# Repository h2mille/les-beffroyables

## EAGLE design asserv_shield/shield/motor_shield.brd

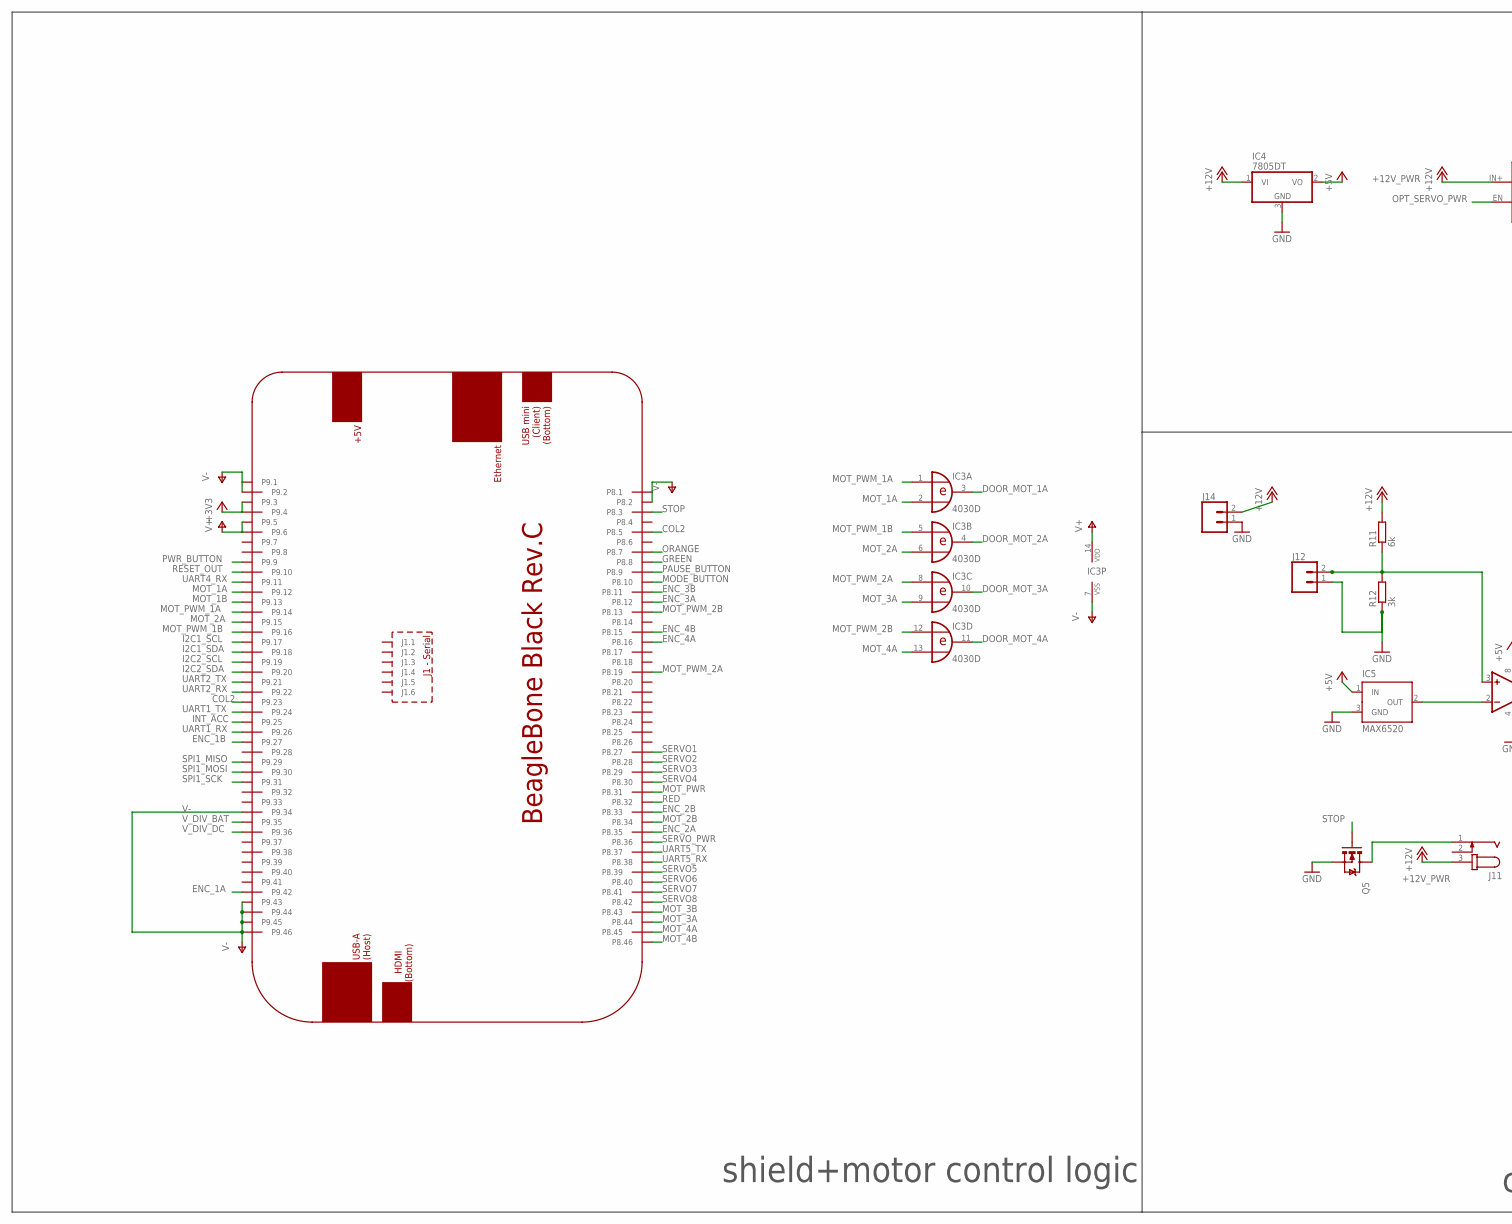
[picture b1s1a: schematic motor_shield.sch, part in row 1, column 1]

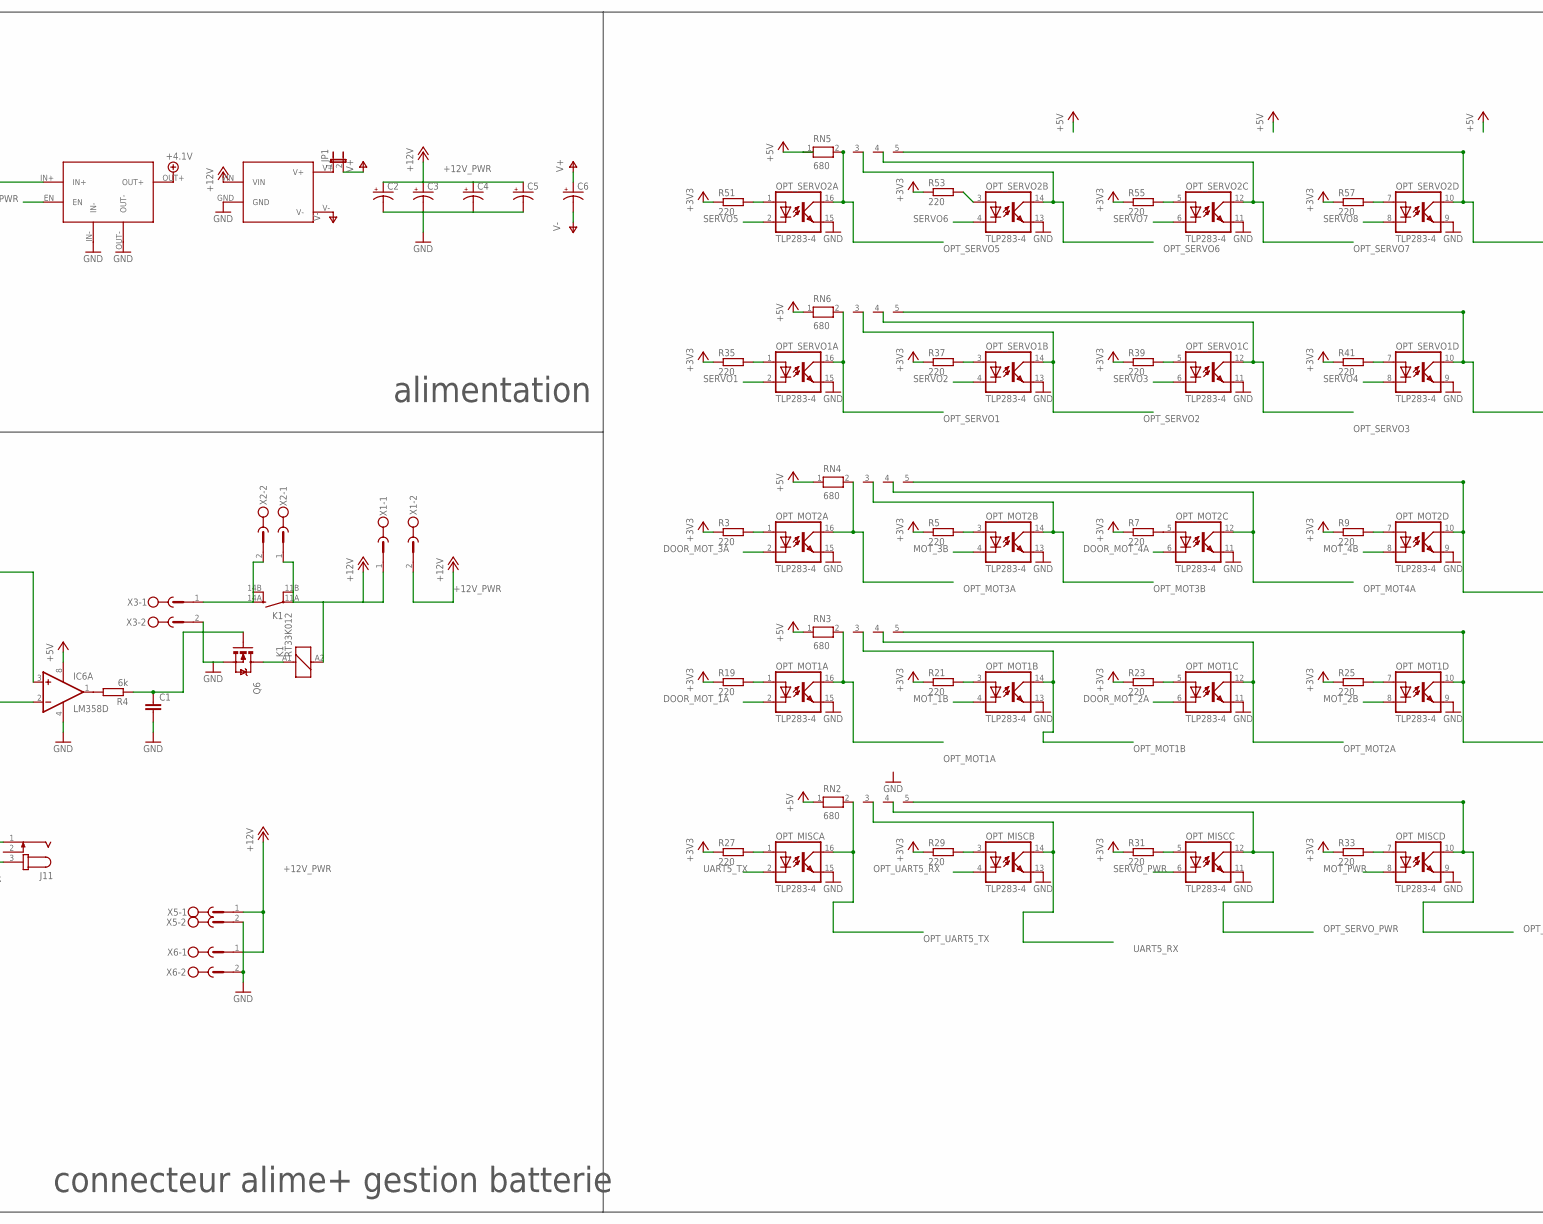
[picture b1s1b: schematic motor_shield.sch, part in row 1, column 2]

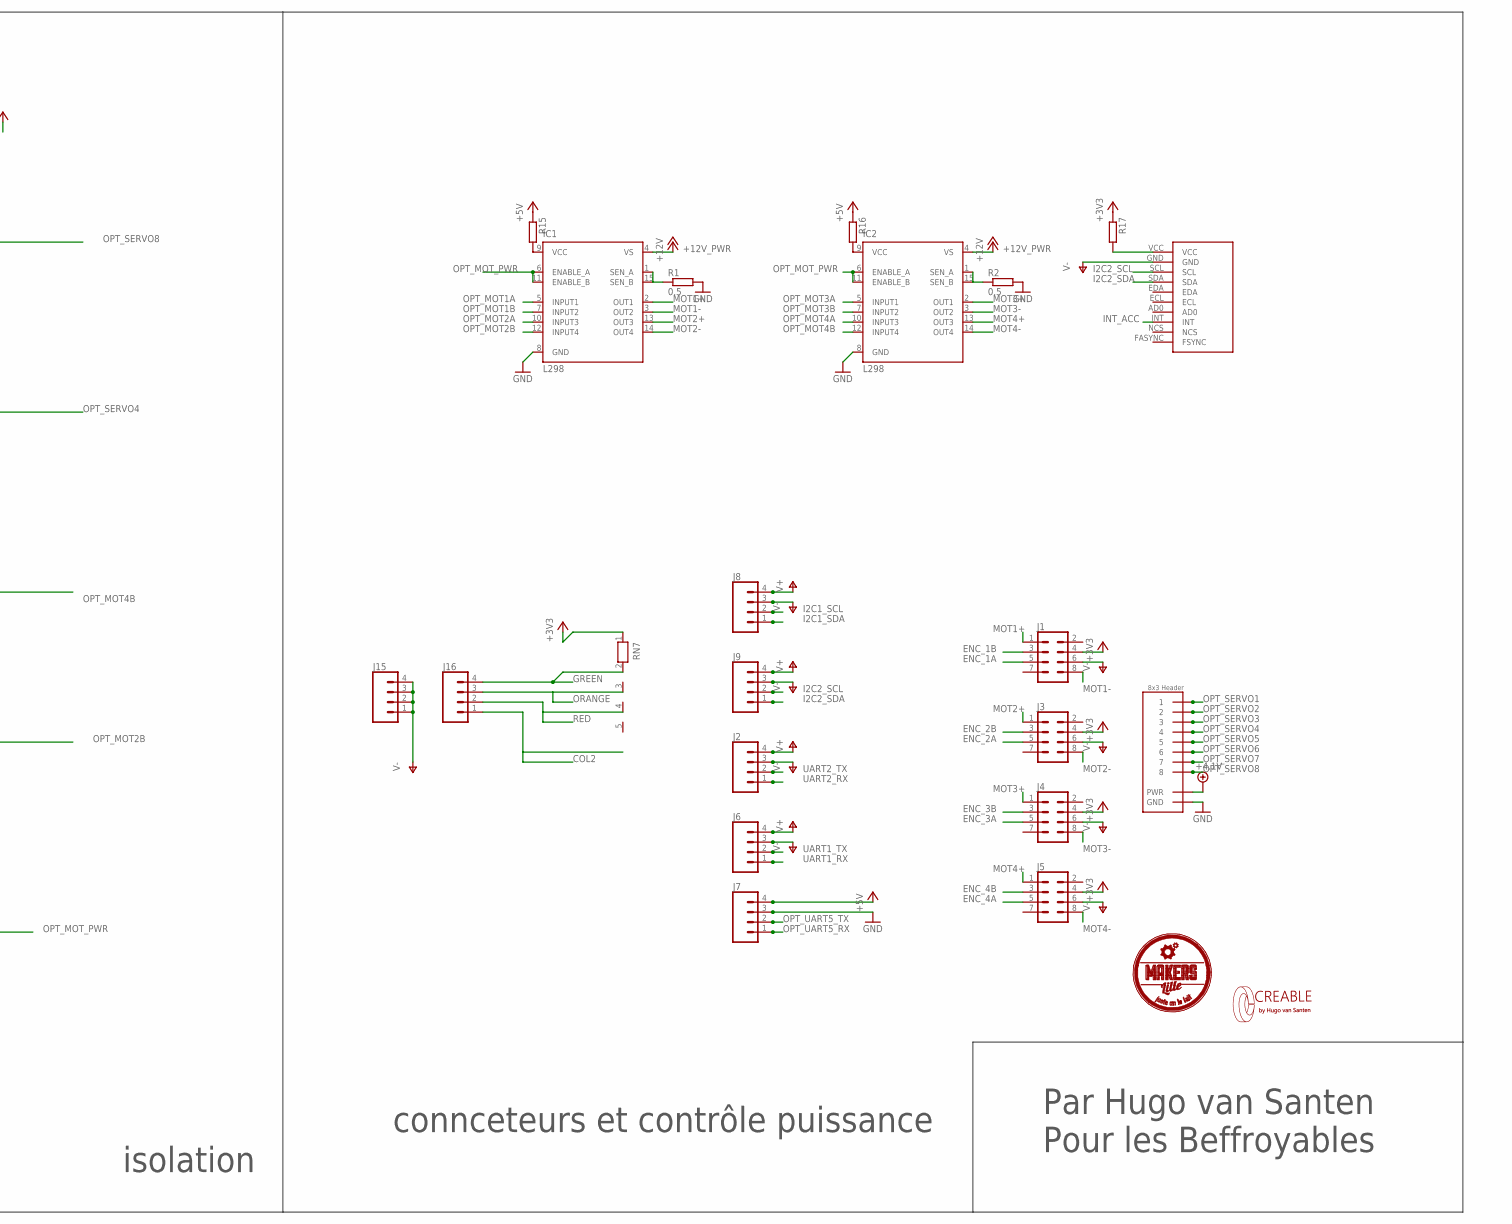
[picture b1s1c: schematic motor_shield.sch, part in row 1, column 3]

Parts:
C1: SPARKFUN-CAPACITORS_CAP0805; SPARKFUN-CAPACITORS_0805
C2, C3, C4, C5, C6: CPOL-US140CLH-1010; ADAFRUIT_140CLH-1010
IC1, IC2: L298; MULTIWATT-15
IC3: 4030D; SO14
IC4: 7805DT; TO252
IC5: MAX6520; SOT23
IC6: LM358D; SO08
J1, J3, J4, J5: CONN_04X2; 2X4
J2, J6, J7, J8, J9: CONN_04POLAR; MOLEX-1X4
J11: JACK-PLUG1; SPC4078
J12, J14: CONN_02POLAR_LOCK; MOLEX-1X2_LOCK
J15, J16: CONN_04; 1X04
JP1: JP1E; JP1
K1: RT33K012; RT-N/O16A5
OPT_MISC: TLP283-4; MINI-FLAT-16
OPT_MOT1, OPT_MOT2: TLP283-4; MINI-FLAT-16
OPT_SERVO1, OPT_SERVO2: TLP283-4; MINI-FLAT-16
PCB1: BEAGLEBONE_BLACK_CAPE
Q5, Q6: STRAWSON_EAGLE_LIB_MOSFET-NCHANNEL; STRAWSON_EAGLE_LIB_SO08-TIGHT
R1, R2: 0.5; M0805
R3, R5, R7, R9, R19, R21, R23, R25, R27, R29, R31, R33, R35, R37, R39, R41, R51, R53, R55, R57: 220; M0805
R4, R11: 6k; M0805
R12: 3k; M0805
R15, R16, R17: R-EU_R0402; R0402
RN2, RN3, RN4, RN5, RN6: 680; RN-5
RN7: RN04; RN-5
U$1: WRA-YMD
U$2: MPU9220; MPU9250
U$3: LOGO
U$4: STRAWSON_EAGLE_LIB_SERVO_HEADERS_8X; STRAWSON_EAGLE_LIB_3X8_0.1"_HEADER
U$5: XL6009
U$6: LOGO_MAKERS
X1, X2, X3, X5, X6: MSTBV2

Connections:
+3V3: J1.4, J3.4, J4.4, J5.4, PCB1.P9.3, PCB1.P9.4, R3.1, R5.1, R7.1, R9.1, R17.1, R19.1, R21.1, R23.1, R25.1, R27.1, R29.1, R31.1, R33.1, R35.1, R37.1, R39.1, R41.1, R51.1, R53.1, R55.1, R57.1, RN7.1
+4.1V: U$4.P$7 (PWR), U$4.P$8 (PWR), U$4.P$9 (PWR), U$4.P$10 (PWR), U$4.P$11 (PWR), U$4.P$12 (PWR), U$4.P$21 (PWR), U$4.P$22 (PWR), U$5.OUT+
+5V: IC4.2 (VO), IC5.1 (IN), IC6.8 (V+), J7.4, R15.1, R16.1, RN2.1, RN3.1, RN4.1, RN5.1, RN6.1
+12V: IC4.1 (VI), J14.2, K1.11A (PA), K1.11B (PB), K1.A2 (2), R11.2, U$1.VIN, X1.1, X2.1
+12V_PWR: C2.+, C3.+, C4.+, C5.+, IC1.4 (VS), IC2.4 (VS), J11.3, U$5.IN+, X1.2, X5.1, X6.1
COL2: J16.1, PCB1.P8.5, PCB1.P9.23
DOOR_MOT_1A: IC3.3 (O), OPT_MOT1.2 (C)
DOOR_MOT_2A: IC3.4 (O), OPT_MOT1.6 (C)
DOOR_MOT_3A: IC3.10 (O), OPT_MOT2.2 (C)
DOOR_MOT_4A: IC3.11 (O), OPT_MOT2.6 (C)
ENC_1A: J1.5, PCB1.P9.42
ENC_1B: J1.3, PCB1.P9.27
ENC_2A: J3.5, PCB1.P8.35
ENC_2B: J3.3, PCB1.P8.33
ENC_3A: J4.5, PCB1.P8.12
ENC_3B: J4.3, PCB1.P8.11
ENC_4A: J5.5, PCB1.P8.16
ENC_4B: J5.3, PCB1.P8.15
GND: C1.2, C2.-, C3.-, C4.-, C5.-, IC1.8 (GND), IC2.8 (GND), IC4.3 (GND), IC5.3 (GND), IC6.4 (V-), J7.3, J12.1, J14.1, OPT_MISC.9 (EMIT), OPT_MISC.11 (EMIT), OPT_MISC.13 (EMIT), OPT_MISC.15 (EMIT), OPT_MOT1.9 (EMIT), OPT_MOT1.11 (EMIT), OPT_MOT1.13 (EMIT), OPT_MOT1.15 (EMIT), OPT_MOT2.9 (EMIT), OPT_MOT2.11 (EMIT), OPT_MOT2.13 (EMIT), OPT_MOT2.15 (EMIT), OPT_SERVO1.9 (EMIT), OPT_SERVO1.11 (EMIT), OPT_SERVO1.13 (EMIT), OPT_SERVO1.15 (EMIT), OPT_SERVO2.9 (EMIT), OPT_SERVO2.11 (EMIT), OPT_SERVO2.13 (EMIT), OPT_SERVO2.15 (EMIT), Q5.1 (S), Q5.2 (S), Q5.3 (S), Q6.1 (S), Q6.2 (S), Q6.3 (S), R1.2, R2.2, R12.1, U$1.GND, U$4.P$13 (GND), U$4.P$14 (GND), U$4.P$15 (GND), U$4.P$16 (GND), U$4.P$17 (GND), U$4.P$18 (GND), U$4.P$23 (GND), U$4.P$24 (GND), U$5.IN-, U$5.OUT-, X3.2, X5.2, X6.2
GREEN: J16.4, PCB1.P8.8, RN7.2
I2C1_SCL: J8.2, PCB1.P9.17
I2C1_SDA: J8.1, PCB1.P9.18
I2C2_SCL: J9.2, PCB1.P9.19, U$2.SCL
I2C2_SDA: J9.1, PCB1.P9.20, U$2.SDA
INT_ACC: PCB1.P9.25, U$2.INT
MODE_BUTTON: PCB1.P8.10
MOT1+: IC1.2 (OUT1), J1.1
MOT1-: IC1.3 (OUT2), J1.8
MOT2+: IC1.13 (OUT3), J3.1
MOT2-: IC1.14 (OUT4), J3.8
MOT3+: IC2.2 (OUT1), J4.1
MOT3-: IC2.3 (OUT2), J4.8
MOT4+: IC2.13 (OUT3), J5.1
MOT4-: IC2.14 (OUT4), J5.8
MOT_1A: IC3.2 (I1), PCB1.P9.12
MOT_1B: OPT_MOT1.4 (C), PCB1.P9.13
MOT_2A: IC3.6 (I1), PCB1.P9.15
MOT_2B: OPT_MOT1.8 (C), PCB1.P8.34
MOT_3A: IC3.9 (I1), PCB1.P8.44
MOT_3B: OPT_MOT2.4 (C), PCB1.P8.43
MOT_4A: IC3.13 (I1), PCB1.P8.45
MOT_4B: OPT_MOT2.8 (C), PCB1.P8.46
MOT_PWM_1A: IC3.1 (I0), PCB1.P9.14
MOT_PWM_1B: IC3.5 (I0), PCB1.P9.16
MOT_PWM_2A: IC3.8 (I0), PCB1.P8.19
MOT_PWM_2B: IC3.12 (I0), PCB1.P8.13
MOT_PWR: OPT_MISC.8 (C), PCB1.P8.31
unnamed: OPT_SERVO2.1 (A), R51.2
unnamed: OPT_SERVO2.3 (A), R53.2
unnamed: OPT_MISC.1 (A), R27.2
unnamed: IC1.1 (SEN_A), IC1.15 (SEN_B), R1.1
unnamed: IC2.1 (SEN_A), IC2.15 (SEN_B), R2.1
unnamed: OPT_SERVO2.7 (A), R57.2
unnamed: OPT_SERVO1.1 (A), R35.2
unnamed: OPT_MOT2.5 (A), R7.2
unnamed: J11.1, Q5.5 (D), Q5.6 (D), Q5.7 (D), Q5.8 (D)
unnamed: OPT_SERVO1.3 (A), R37.2
unnamed: OPT_SERVO1.7 (A), R41.2
unnamed: OPT_MOT2.1 (A), R3.2
unnamed: OPT_MOT2.3 (A), R5.2
unnamed: OPT_MOT2.7 (A), R9.2
unnamed: OPT_MOT1.3 (A), R21.2
unnamed: OPT_MOT1.1 (A), R19.2
unnamed: OPT_MOT1.7 (A), R25.2
unnamed: OPT_MOT1.5 (A), R23.2
unnamed: OPT_SERVO1.5 (A), R39.2
unnamed: OPT_MISC.3 (A), R29.2
unnamed: OPT_MISC.7 (A), R33.2
unnamed: OPT_SERVO2.5 (A), R55.2
unnamed: IC5.2 (OUT), IC6.2 (-IN)
unnamed: OPT_MISC.5 (A), R31.2
unnamed: IC6.1 (OUT), R4.2
unnamed: K1.14A (SA), K1.14B (SB), X2.2, X3.1
unnamed: K1.A1 (1), Q6.5 (D), Q6.6 (D), Q6.7 (D), Q6.8 (D)
unnamed: IC6.3 (+IN), J12.2, R11.1, R12.2
unnamed: C1.1, Q6.4 (G), R4.1
unnamed: JP1.1, U$1.V+
unnamed: IC1.9 (VCC), R15.2
unnamed: IC2.9 (VCC), R16.2
unnamed: R17.2, U$2.VCC
OPT_MOT1A: IC1.5 (INPUT1), OPT_MOT1.16 (COL), RN3.2
OPT_MOT1B: IC1.7 (INPUT2), OPT_MOT1.14 (COL), RN3.3
OPT_MOT2A: IC1.10 (INPUT3), OPT_MOT1.12 (COL), RN3.4
OPT_MOT2B: IC1.12 (INPUT4), OPT_MOT1.10 (COL), RN3.5
OPT_MOT3A: IC2.5 (INPUT1), OPT_MOT2.16 (COL), RN4.2
OPT_MOT3B: IC2.7 (INPUT2), OPT_MOT2.14 (COL), RN4.3
OPT_MOT4A: IC2.10 (INPUT3), OPT_MOT2.12 (COL), RN4.4
OPT_MOT4B: IC2.12 (INPUT4), OPT_MOT2.10 (COL), RN4.5
OPT_MOT_PWR: IC1.6 (ENABLE_A), IC1.11 (ENABLE_B), IC2.6 (ENABLE_A), IC2.11 (ENABLE_B), OPT_MISC.10 (COL), RN2.5
OPT_SERVO1: OPT_SERVO1.16 (COL), RN6.2, U$4.P$1 (1)
OPT_SERVO2: OPT_SERVO1.14 (COL), RN6.3, U$4.P$2 (2)
OPT_SERVO3: OPT_SERVO1.12 (COL), RN6.4, U$4.P$3 (3)
OPT_SERVO4: OPT_SERVO1.10 (COL), RN6.5, U$4.P$4 (4)
OPT_SERVO5: OPT_SERVO2.16 (COL), RN5.2, U$4.P$5 (5)
OPT_SERVO6: OPT_SERVO2.14 (COL), RN5.3, U$4.P$6 (6)
OPT_SERVO7: OPT_SERVO2.12 (COL), RN5.4, U$4.P$19 (7)
OPT_SERVO8: OPT_SERVO2.10 (COL), RN5.5, U$4.P$20 (8)
OPT_SERVO_PWR: OPT_MISC.12 (COL), RN2.4, U$5.EN
OPT_UART5_RX: J7.1, OPT_MISC.4 (C)
OPT_UART5_TX: J7.2, OPT_MISC.16 (COL), RN2.2
ORANGE: J16.3, PCB1.P8.7, RN7.3
PAUSE_BUTTON: PCB1.P8.9
PWR_BUTTON: PCB1.P9.9
RED: J16.2, PCB1.P8.32, RN7.4
RESET_OUT: PCB1.P9.10
SERVO1: OPT_SERVO1.2 (C), PCB1.P8.27
SERVO2: OPT_SERVO1.4 (C), PCB1.P8.28
SERVO3: OPT_SERVO1.6 (C), PCB1.P8.29
SERVO4: OPT_SERVO1.8 (C), PCB1.P8.30
SERVO5: OPT_SERVO2.2 (C), PCB1.P8.39
SERVO6: OPT_SERVO2.4 (C), PCB1.P8.40
SERVO7: OPT_SERVO2.6 (C), PCB1.P8.41
SERVO8: OPT_SERVO2.8 (C), PCB1.P8.42
SERVO_PWR: OPT_MISC.6 (C), PCB1.P8.36
SPI1_MISO: PCB1.P9.29
SPI1_MOSI: PCB1.P9.30
SPI1_SCK: PCB1.P9.31
STOP: PCB1.P8.3, Q5.4 (G)
UART1_RX: J6.1, PCB1.P9.26
UART1_TX: J6.2, PCB1.P9.24
UART2_RX: J2.1, PCB1.P9.22
UART2_TX: J2.2, PCB1.P9.21
UART4_RX: PCB1.P9.11
UART5_RX: OPT_MISC.14 (COL), PCB1.P8.38, RN2.3
UART5_TX: OPT_MISC.2 (C), PCB1.P8.37
V+: C6.+, IC3.14 (VDD), J2.4, J6.4, J8.4, J9.4, JP1.2, PCB1.P9.5, PCB1.P9.6
V-: C6.-, IC3.7 (VSS), J1.6, J2.3, J3.6, J4.6, J5.6, J6.3, J8.3, J9.3, J15.1, J15.2, J15.3, J15.4, PCB1.P8.1, PCB1.P8.2, PCB1.P9.1, PCB1.P9.2, PCB1.P9.34, PCB1.P9.43, PCB1.P9.44, PCB1.P9.45, PCB1.P9.46, U$1.V-, U$2.GND
V_DIV_BAT: PCB1.P9.35
V_DIV_DC: PCB1.P9.36

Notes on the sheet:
shield+motor control logic
alimentation
connecteur alime+ gestion batterie
isolation
connceteurs et contrôle puissance
Par Hugo van Santen Pour les Beffroyables

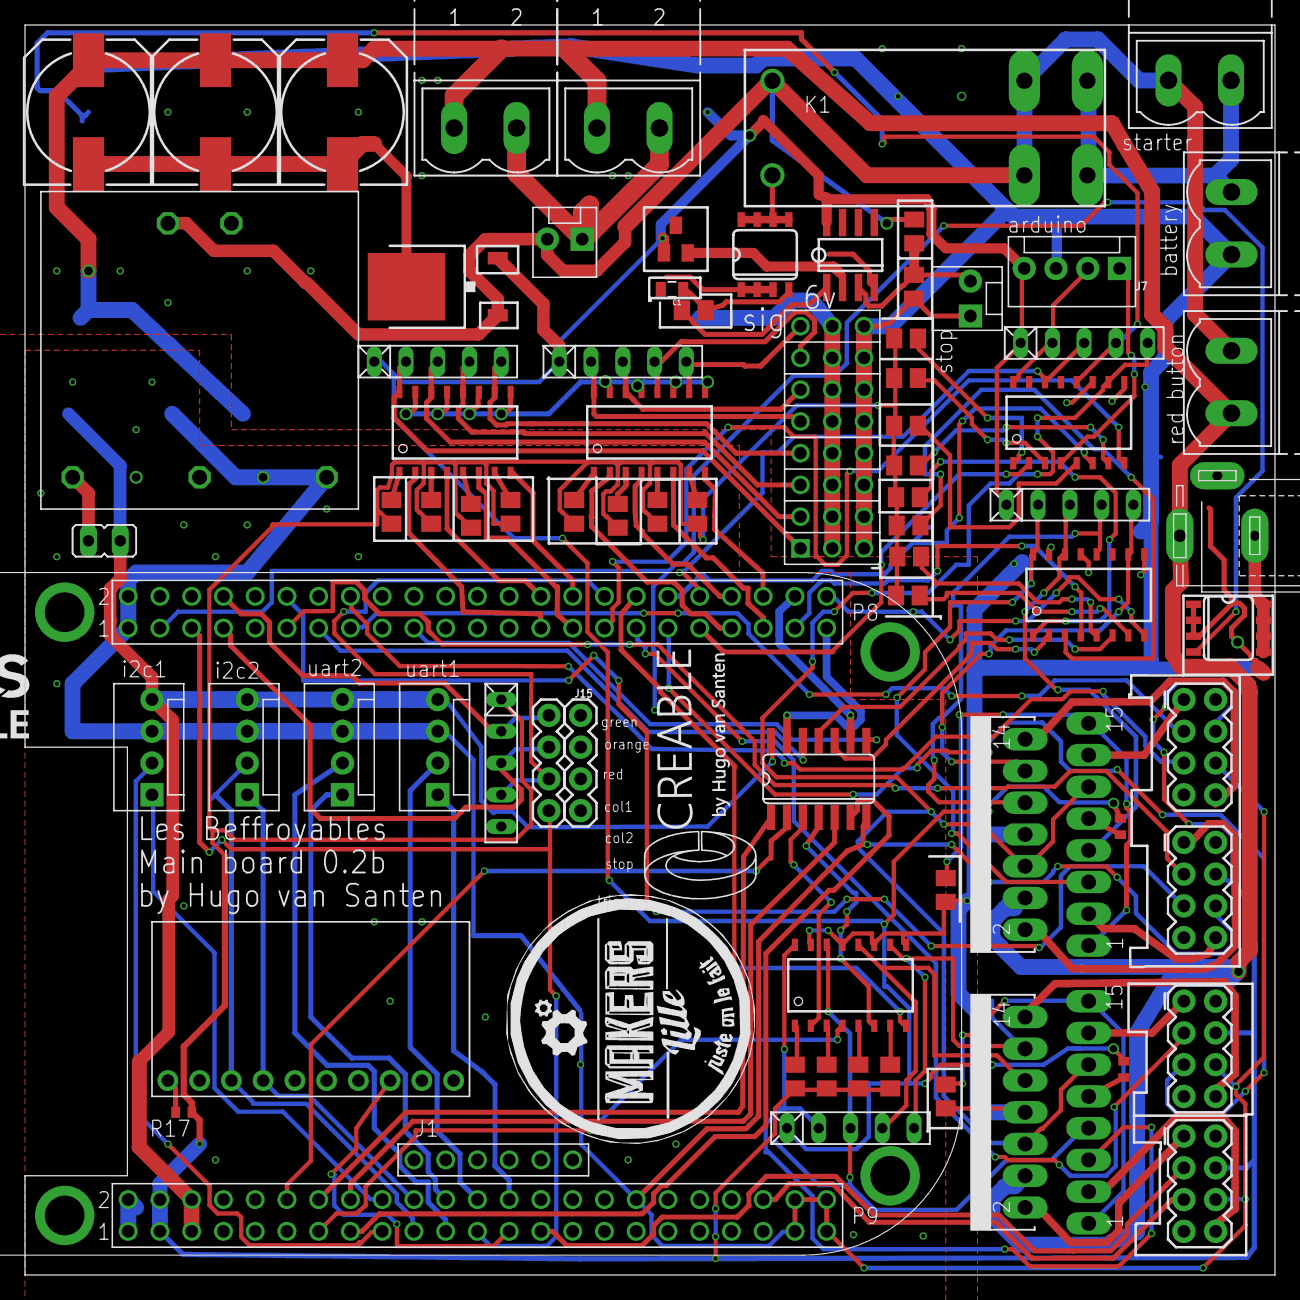
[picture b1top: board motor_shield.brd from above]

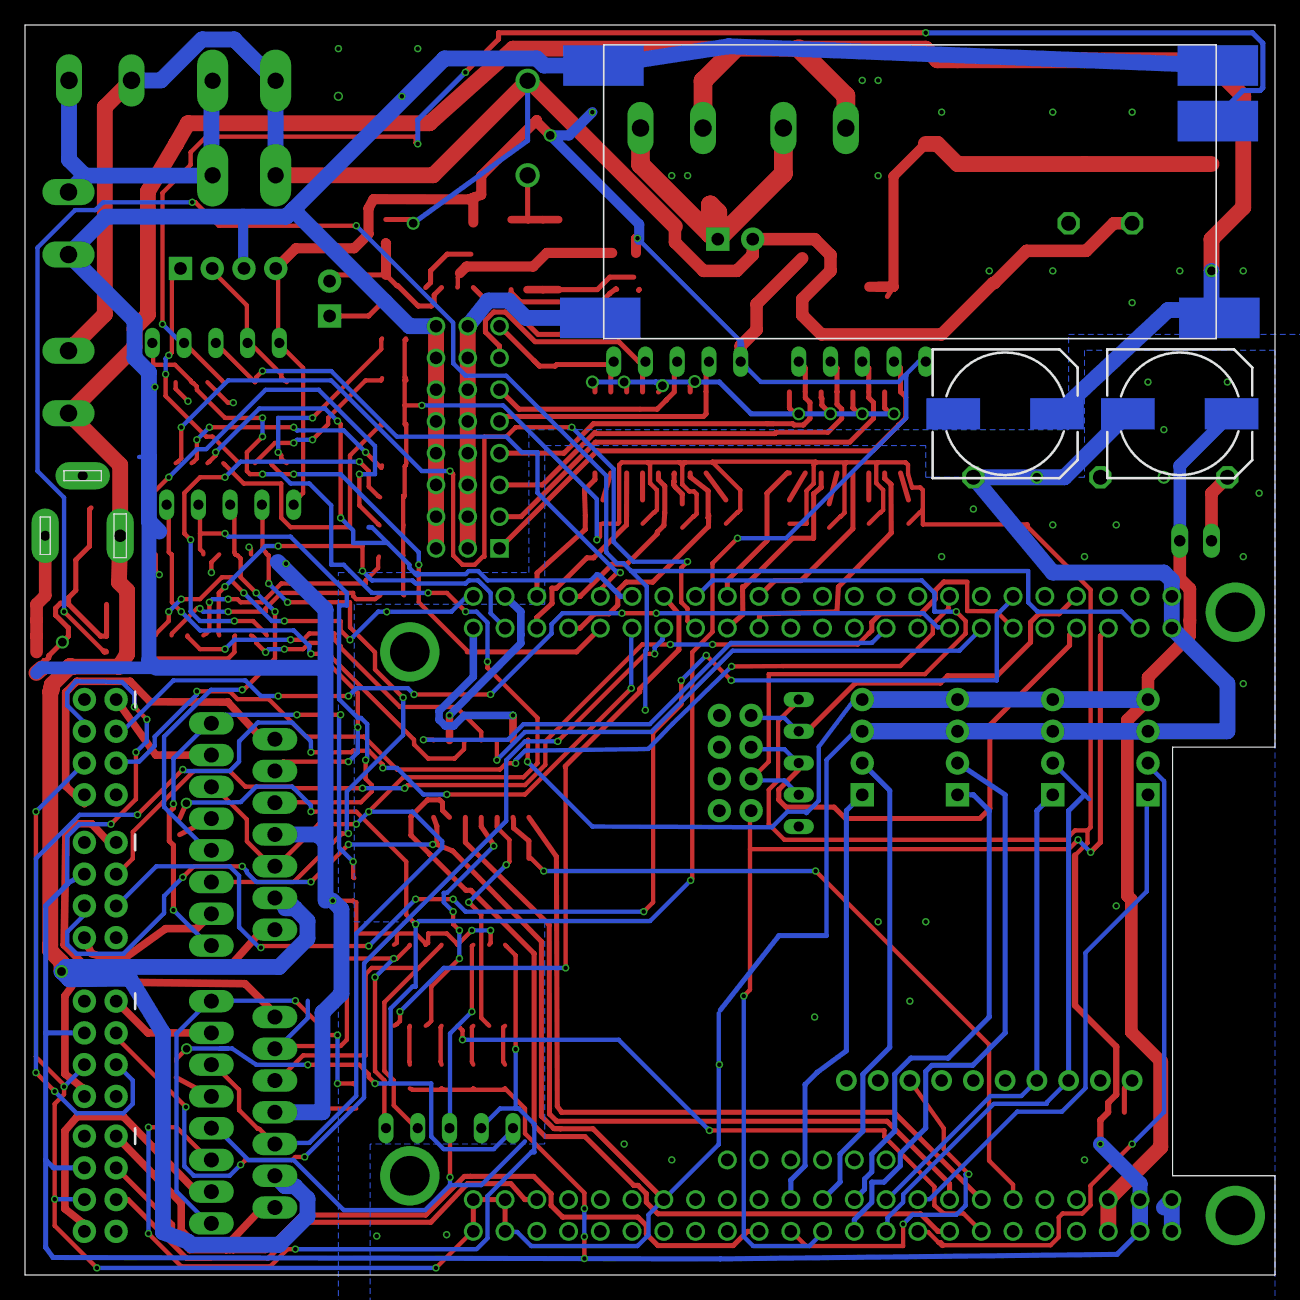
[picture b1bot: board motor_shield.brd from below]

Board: 2 copper layers, 100.0 x 100.0 mm, 81 parts (3 on the bottom side), 119 nets.

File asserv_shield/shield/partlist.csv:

Parts;Device;Qty;link;Value;Package;;Description;MF;MPN;OC_FARNELL;OC_NEWARK;PROD_ID;SF_ID;SPICEPREFIX
J12, J14;CONN_02POLAR_LOCK;2;;;MOLEX-1X2_LOCK;;Multi connection point. Often used as Generic Header-pin footprint for 0.1 inch spaced/style header connections;;;;;;PRT-09918;
J15, J16;CONN_04;2;;;1X04;;Multi connection point. Often used as Generic Header-pin footprint for 0.1 inch spaced/style header connections;;;;;CONN-09696;;
J2, J6, J7, J8, J9;CONN_04POLAR;5;;;MOLEX-1X4;;Multi connection point. Often used as Generic Header-pin footprint for 0.1 inch spaced/style header connections;;;;;CONN-08186;PRT-08231;
J1, J3, J4, J5;CONN_04X2;4;;;2X4;;Multi connection point. Often used as Generic Header-pin footprint for 0.1 inch spaced/style header connections;;;;;;;
C2, C3, C4, C5, C6;CPOL-US140CLH-1010;5;;;ADAFRUIT_140CLH-1010;;POLARIZED CAPACITOR, American symbol;;;;;;;
J11;JACK-PLUG1;1;;;SPC4078;;DC POWER JACK;;;unknown;unknown;;;
JP1;JP1E;1;;;JP1;;JUMPER;;;;;;;
X1, X2, X3, X5, X6;MSTBV2;5;;;MSTBV2;;PHOENIX;;;unknown;unknown;;;
R15, R16, R17;R-EU_R0402;3;;;R0402;;RESISTOR, European symbol;;;;;;;
RN7;RN04;1;;;RN-5;;RESISTOR NETWORK;;;unknown;unknown;;;
C1;SPARKFUN-CAPACITORS_CAP0805;1;;;SPARKFUN-CAPACITORS_0805;;Capacitor;;;;;;;
R1, R2;R-EU_M0805;2;;0.5;M0805;;RESISTOR, European symbol;;;;;;;R
R3, R5, R7, R9, R19, R21, R23, R25, R27, R29, R31, R33, R35, R37, R39, R41, R51, R53, R55, R57;R-EU_M0805;20;;220;M0805;;RESISTOR, European symbol;;;;;;;R
R12;R-EU_M0805;1;;3k;M0805;;RESISTOR, European symbol;;;;;;;R
IC3;4030D;1;;4030D;SO14;;Quad XOR;;;;;;;
RN2, RN3, RN4, RN5, RN6;RN04;5;;680;RN-5;;RESISTOR NETWORK;;;unknown;unknown;;;
R4, R11;R-EU_M0805;2;;6k;M0805;;RESISTOR, European symbol;;;;;;;R
IC4;7805DT;1;;7805DT;TO252;;Positive VOLTAGE REGULATOR;;;;;;;
PCB1;BEAGLEBONE_BLACK_CAPE;1;;BEAGLEBONE_BLACK_CAPE;BEAGLEBONE_BLACK_CAPE;;;;;;;;;
IC1, IC2;L298;2;;L298;MULTIWATT-15;;DUAL FULL-BRIDGE DRIVER;;L298N;1589425;32M1527;;;
IC6;LM358D;1;;LM358D;SO08;;"OP AMP also LM158; LM258; LM2904";;;;;;;
IC5;MAX6520;1;;MAX6520;SOT23;;1.2V Voltage Reference 50ppm/°C, SOT23, 3-Terminal;MAXIM;MAX6520EUR-T;unknown;02J4586;;;
U$2;MPU9220;1;;MPU9220;MPU9250;;;;;;;;;
K1;RT33K012;1;;RT33K012;RT-N/O16A5;;Power PCB Relay Inrush  SCHRACK;;RT33K012;unknown;48M7964;;;
Q5, Q6;STRAWSON_EAGLE_LIB_MOSFET-NCHANNEL;2;;STRAWSON_EAGLE_LIB_MOSFET-NCHANNEL;STRAWSON_EAGLE_LIB_SO08-TIGHT;;Common NMOSFET Parts;;;;;;;
U$4;STRAWSON_EAGLE_LIB_SERVO_HEADERS_8X;1;;STRAWSON_EAGLE_LIB_SERVO_HEADERS_8X;"STRAWSON_EAGLE_LIB_3X8_0.1_HEADER""";;;;;;;;;
OPT_MISC, OPT_MOT1, OPT_MOT2, OPT_SERVO1, OPT_SERVO2;TLP283-4;5;;TLP283-4;MINI-FLAT-16;;TOSHIBA PHOTOCOUPLER GaAs IRED & PHOTO-TRANSISTOR;;;unknown;unknown;;;
U$1;WRA-YMD;1;;WRA-YMD;WRA-YMD;;;;;;;;;
U$5;XL6009;1;;XL6009;XL6009;;;;;;;;;

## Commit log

2018-02-14 1st commit, mostly working
    asser, making nice squares
2018-02-14 missing cmake file
    here is the main CMakeLists
2018-02-19 add stack trip
2018-02-19 Revert "add stack trip"
    This reverts commit ee5e98a24f767012e379136e13f998f4ae021e31.
2018-02-19 no need parameter here
2018-02-20 solivng stacked moves better
    now it makes nice circles!
2018-02-21 solving some distance issue
2018-02-26 ajout mécanique
    dont fichier empty car un répertoire ne peut être vide
2018-02-26 ajout méca
2018-02-26 rangement cube dans son repertoire
2018-02-26 add board on work
2018-02-28 PCB v0.1
2018-03-01 minor updates
2018-03-01 présentation schematics
2018-03-02 ajout télémétrie
    commence à être fonctionnel!
2018-03-05 slower more acuurante rate, and continuous measurement
2018-03-23 coorection board
    modification board:
    -correction alim découpage
    -correction découpe contour
    -correction ligne optocoupleur servo_enable
    -correction ligne arduino imu
    -amélioration connecteurs boutons
2018-04-02 télémetrie+affichage
    affichage distance sur écran LCD
    Test de la librairie Adafruit, basée directement sur celle de ST, mais hyper lourde, trop pour un arduino uno avec 3 capteurs, fail à 2 capteurs, et fonctionne pour un capteur. Je conseil la librairi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
    Les infos supplémentaires de mesure sur la librairie Adafruit ne sont pas particulièrement utilie.
2018-04-02 change directory
2018-04-04 meilleur filtre valeurs capteurs
2018-04-04 add quick parser with named FIFO
    still the beginning
2018-04-07 Centrale issue solved, parsing on good way
2018-04-15 parser improvement
    add many functions, such as
    control independant motor
    control servos
    etc...
2018-04-19 ajout IA+correction bugs mineurs
2018-04-24 v0 télémétrie
2018-05-06 ajout bouton rouge
2018-05-07 capteur interuption 40cm
2018-05-07 ajout driver écran modifié
2018-05-13 after cup
2018-05-16 communication parfaite
    communication plus rapide, possible via web et via plusieurs canaux.
2018-05-25 add hardware pdf
2019-06-10 2019 after eurobot

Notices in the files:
parts and their libraries:
SparkFun-Connectors: Licensing: Creative Commons ShareAlike 4.0 International - https://creativecommons.org/licenses/by-sa/4.0
